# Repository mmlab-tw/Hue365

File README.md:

# Hue365

A color-changeable light on a piece of paper.

Instructions can be found below:
https://medium.com/@merlin.mustache/hue365%E4%B8%80%E8%B5%B7%E5%81%9A-f0863da383ad

////// Merlin's Mustache Lab https://mmlab.com.tw/ //////

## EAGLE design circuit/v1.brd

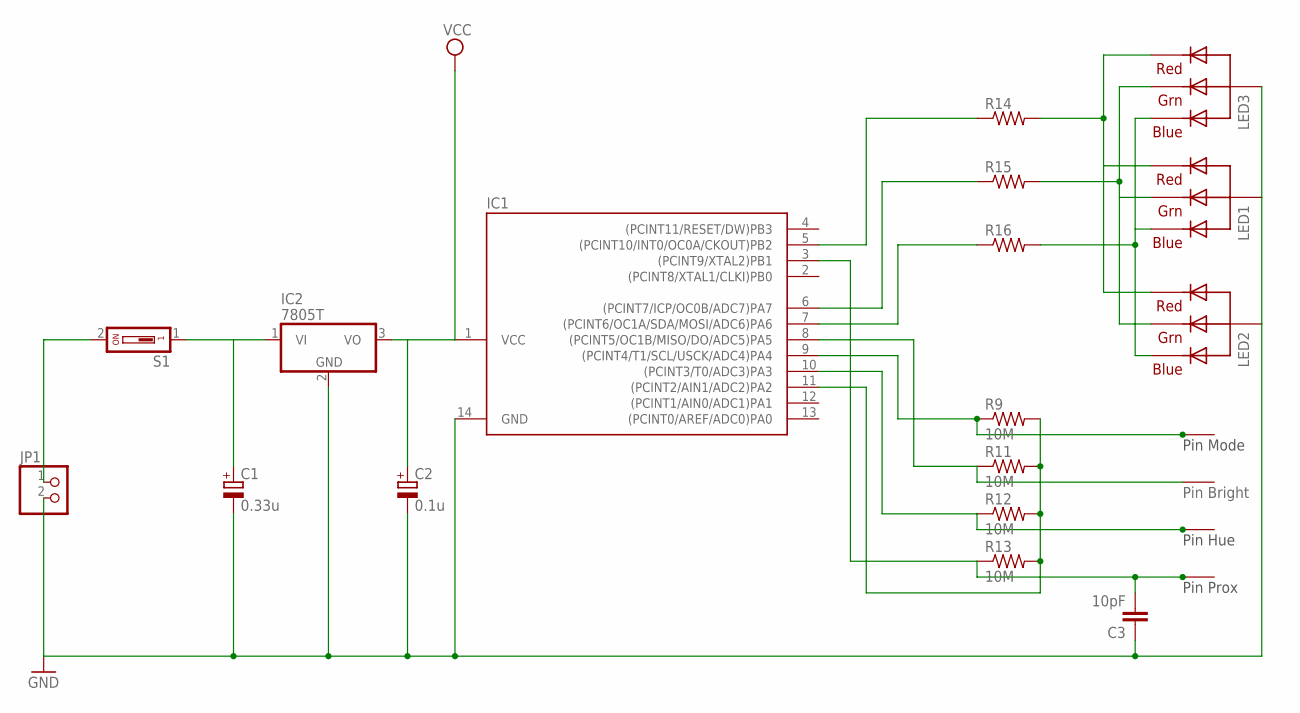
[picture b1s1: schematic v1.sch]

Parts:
2: TOUCH; RENG
C1: 0.33u; E2,5-6
C2: 0.1u; E2,5-6
C3: 10pF; CAP-PTH-SMALL-KIT
IC1: TINY24/44/84-PU; DIL14
IC2: 7805T; TO220H
JP1: PINHD-1X2/90; 1X02/90
LED1, LED2, LED3: RGBLED_CA-5MM; LED5MMRGB
PIN_PROX: TOUCH; RENG
PROX_PIN: TOUCH; RENG
R9, R11, R12, R13: 10M; 0207/10
R14, R15, R16: R-US_0207/10; 0207/10
S1: SD4-01
U$3: TOUCH; RENG

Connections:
B: LED1.4 (BLUE), LED2.4 (BLUE), LED3.4 (BLUE), R16.2
B1: IC1.7 ((PCINT6/OC1A/SDA/MOSI/ADC6)PA6), R16.1
BASE: IC1.11 ((PCINT2/AIN1/ADC2)PA2), R9.2, R11.2, R12.2, R13.2
G: LED1.3 (GREEN), LED2.3 (GREEN), LED3.3 (GREEN), R15.2
G1: IC1.6 ((PCINT7/ICP/OC0B/ADC7)PA7), R15.1
GND: C1.-, C2.-, C3.1, IC1.14 (GND), IC2.2 (GND), JP1.2, LED1.2 (VCC), LED2.2 (VCC), LED3.2 (VCC)
unnamed: JP1.1, S1.2
unnamed: C1.+, IC2.1 (VI), S1.1
PIN0: 2.T, IC1.8 ((PCINT5/OC1B/MISO/DO/ADC5)PA5), R11.1
PIN1: IC1.9 ((PCINT4/T1/SCL/USCK/ADC4)PA4), PIN_PROX.T, R9.1
PIN2: IC1.10 ((PCINT3/T0/ADC3)PA3), R12.1, U$3.T
PIN3: C3.2, IC1.3 ((PCINT9/XTAL2)PB1), PROX_PIN.T, R13.1
R: LED1.1 (RED), LED2.1 (RED), LED3.1 (RED), R14.2
R1: IC1.5 ((PCINT10/INT0/OC0A/CKOUT)PB2), R14.1
VCC: C2.+, IC1.1 (VCC), IC2.3 (VO)

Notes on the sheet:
Pin Prox
Pin Hue
Pin Bright
Pin Mode

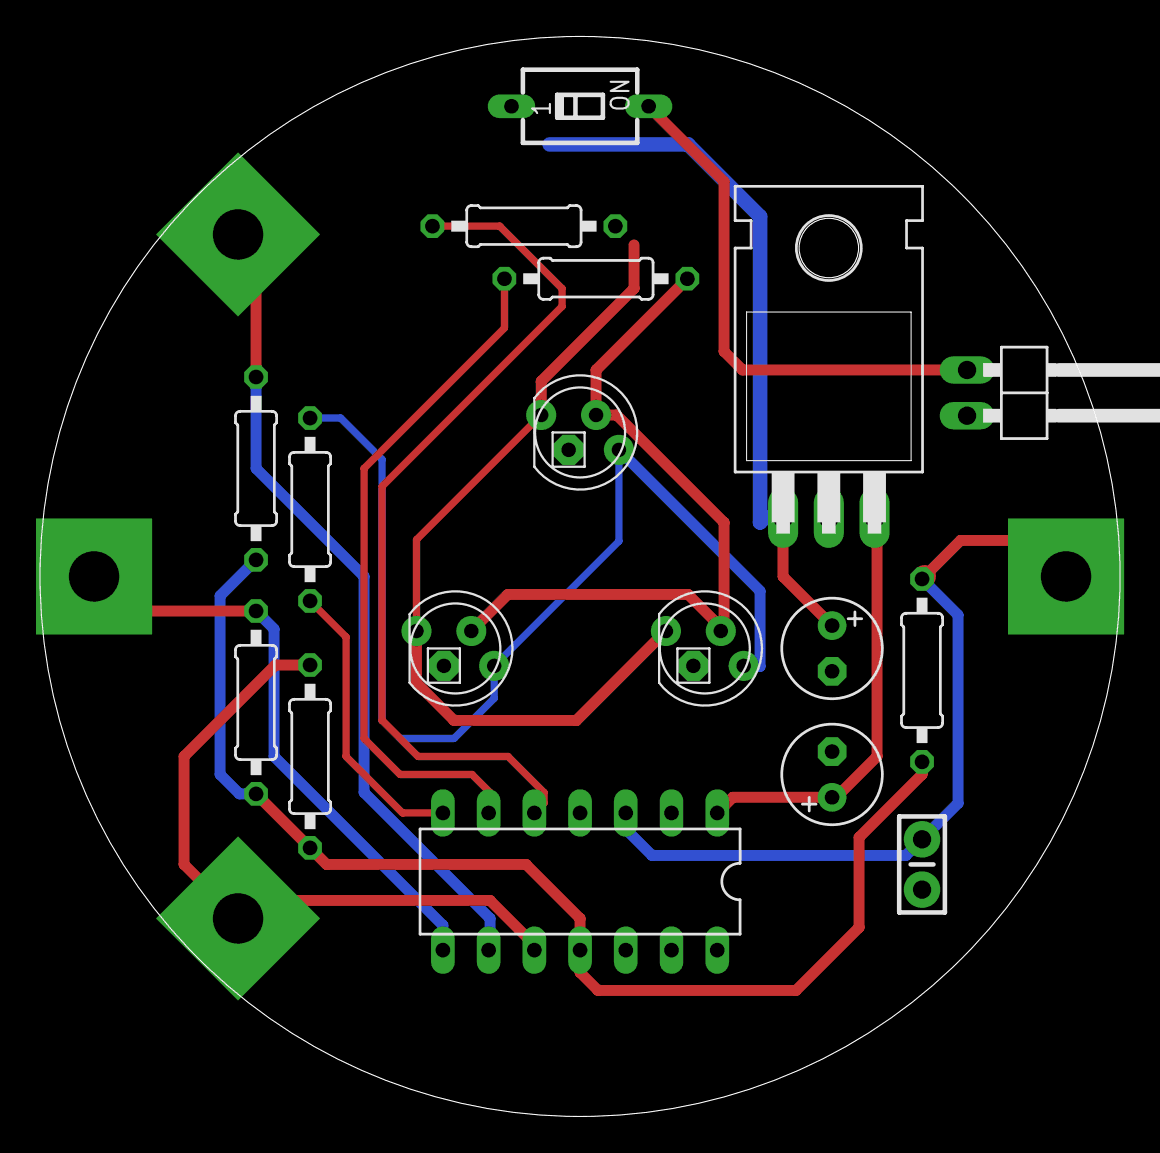
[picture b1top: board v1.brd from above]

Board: 2 copper layers, 60.0 x 60.0 mm, 21 parts (0 on the bottom side), 15 nets.

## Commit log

2018-01-11 add circuit and arduino files
2018-01-12 add print
2018-01-15 Create print

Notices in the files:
parts and their libraries:
SparkFun-Capacitors: Licensing: Creative Commons ShareAlike 4.0 International - https://creativecommons.org/licenses/by-sa/4.0
